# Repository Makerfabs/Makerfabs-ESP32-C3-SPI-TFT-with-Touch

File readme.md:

# Makerfabs ESP32-C3 SPI TFT with Touch

```c++
/*
Version:		V1.3
Author:			Vincent
Create Date:	2022/9/23
Note:
		2022/10/13	V1.1: Add example
		2022/10/18	V1.2: Add Line Chart demo
		2022/12/29	V1.3: Change wiki link
*/
```

[toc]

# Makerfabs

[Makerfabs home page](https://www.makerfabs.com/)

[Makerfabs Wiki](https://wiki.makerfabs.com/)

# Makerfabs ESP32-C3 SPI TFT with Touch
## Intruduce

Product Link ：[ESP32-C3 SPI TFT with Touch 3.5'' ILI9488](https://www.makerfabs.com/ep32-c3-risc-v-spi-tft-touch.html)

Wiki Link : [ESP32-C3_SPI_TFT_with_Touch](https://wiki.makerfabs.com/ESP32_C3_SPI_3.5_TFT_with_Touch.html)

Makerfabs ESP32-C3 TFT Touch equips with ESP32-C3, which is a single-core Wi-Fi and Bluetooth 5 (LE) microcontroller SoC, built around a 32-bit **RISC-V** chip processor with a four-stage pipeline that operates at up to 160 MHz, with 4MB Flash, 400KB SRAM. 

Being a number of the Makerfabs ESP Display family, this ESP32 C3 SPI 3.5 inch Touch is 320*480, with ILI9488 driver. Same as the other Makerfab's ESP32 displays, there 2 USB connectors, one for USB2UART convertor, and 1 USB native; on-board SD card, and Mabee connector(I2C) which is Seeedstudio Grove compatible, so it fits for applications that need sensor connected.

## Feature

- Controller: ESP32-C3-MINI-1-N4, 4MB Flash, RISCV-32bit, 160MHz, 400KB SRAM, Bluetooth 5
- Wireless: WiFi & Bluetooth 5.0
- LCD: 3.5inch TFT LCD
- Resolution: 480*320
- Color: RGB
- LCD interface: SPI
- LCD Driver: ili9488
- Touch Panel: Capacitive
- Touch Panel Driver: FT6236
- USB: Dual USB Type-C(one for USB-to-UART and one for native USB)
- USB2UART Chip: CP2104
- Power Supply: USB Type-C 5.0V(4.0V~5.25V)
- Button: Flash button and reset button
- Mabee interface: 1*I2C
- Backlight Controller: Yes
- MicroSD: Yes
- Arduino support: Yes
- Type-C Power Delivery: Not Supported
- Operation temperature: -40℃ to +85℃
- Dimension: 66mm * 84.3mm * 12mm
- Weight: 52g

# Code Explain

## Complier Option

- Install board : ESP32 .
- Install library : LovyanGFX library. 
- Use type-c use cable connect USB-TTL to PC.
- Upload codes, select "ESP32-C3 DEV Module"

## Firmware

### c3_9488

A simple test procedure. Touch the black area in the middle of the screen, and the screen starts showing solid colors in turn. Finally, an SD card image is displayed.

## Example

### Mabee CO2 Display

SGP30 and SHT31 sensor values are displayed on the screen. Use [Mabee CO2](https://www.makerfabs.com/mabee-tvoc-and-eco2-sgp30-sht31.html) sensor.

Need libraries:

- Adafruit_SGP30
- Adafruit_SHT31

### TVOC line chart

Shows a line chart of TVOC

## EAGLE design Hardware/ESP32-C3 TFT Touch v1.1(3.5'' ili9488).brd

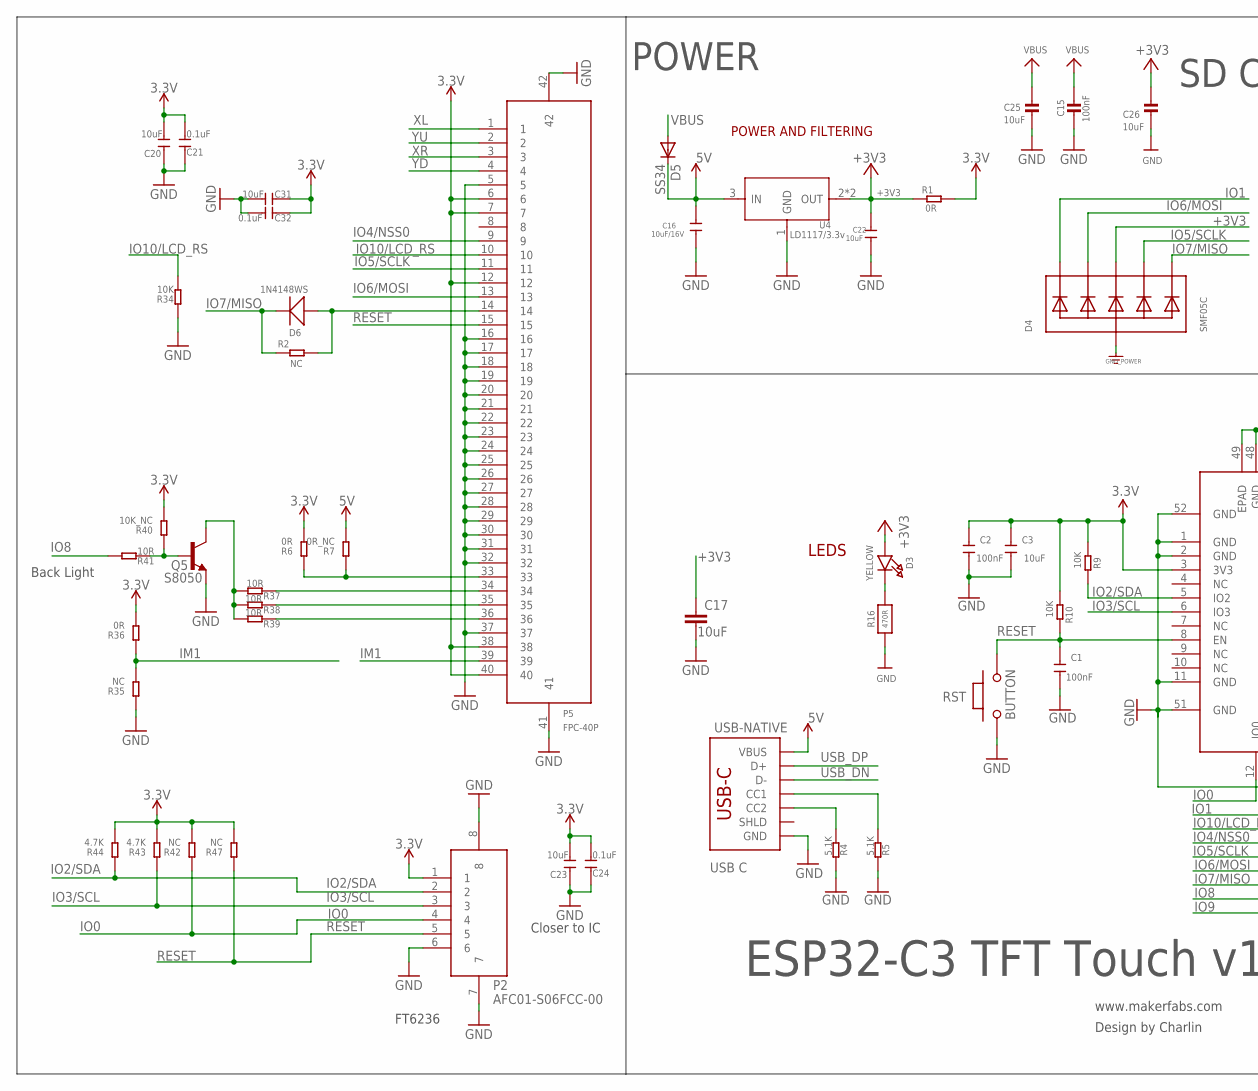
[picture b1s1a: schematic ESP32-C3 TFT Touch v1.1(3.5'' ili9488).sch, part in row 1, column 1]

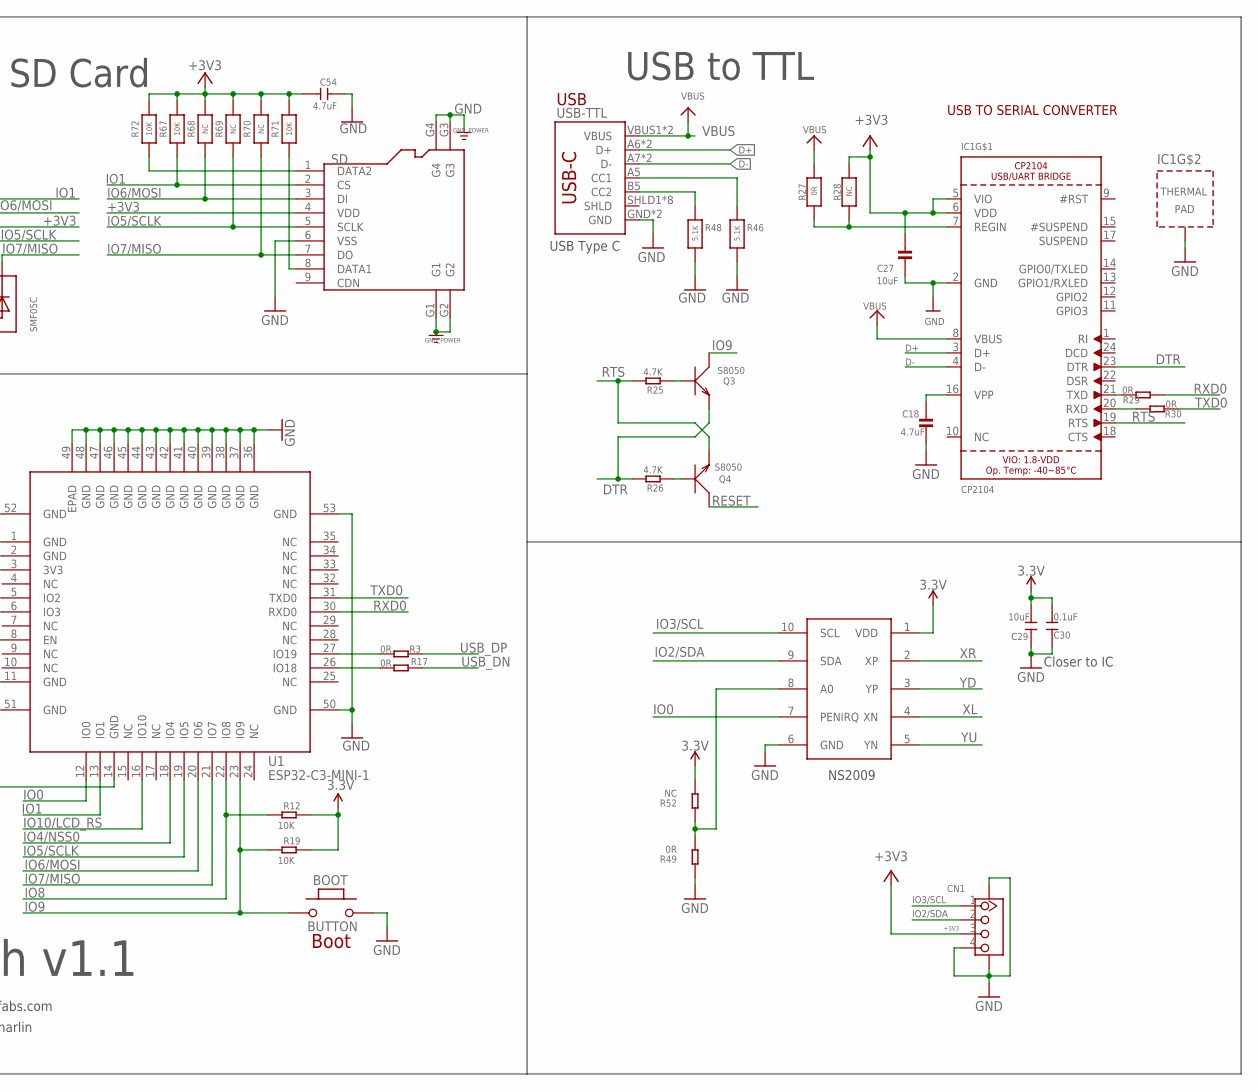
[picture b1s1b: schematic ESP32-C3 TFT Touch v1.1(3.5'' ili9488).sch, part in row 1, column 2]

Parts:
BOOT: BUTTON; 157SW
C1, C2: 100nF; C0603
C3, C17, C22: 10uF; C0603
C15: 100nF; 0603-NO
C16: 10uF/16V; C0603
C18: 4.7uF; 0603-NO
C20, C23, C29, C31: 10uF; DISCRETE_C0603
C21, C24, C30, C32: 0.1uF; DISCRETE_C0603
C25, C26, C27: 10uF; 0603-NO
C54: 4.7uF; DISCRETE_C0603
CN1: GROVE-CONNECTOR-SMD'90D'; HW4-SMD-2.0-90D
D3: YELLOW; CHIPLED_0805_NOOUTLINE
D4: SMF05C; SOT363
D5: SS34; DO-214AC
D6: 1N4148WS; SOD323
IC1: CP2104; QFN24_4MM_SMSC
P2: AFC01-S06FCC-00; SMD8-50P-740L535W
P5: FPC-40P; SMD42-50P-2560L490W
Q3, Q4: S8050; SOT23
Q5: S8050; SPARKFUN_SOT23
R1, R3, R17, R29, R30: 0R; R0603
R2: NC; R0603
R4, R5: 5.1K; R0603
R6, R36, R49: 0R; DISCRETE_R0603
R7: 0R_NC; DISCRETE_R0603
R9, R10, R12, R19: 10K; R0603
R16: 470R; 0603-NO
R25, R26: 4.7K; R0603
R27: 0R; 0603-NO
R28, R68, R69, R70: NC; 0603-NO
R34: 10K; DISCRETE_R0603
R35, R42, R47, R52: NC; DISCRETE_R0603
R37, R38, R39, R41: 10R; DISCRETE_R0603
R40: 10K_NC; DISCRETE_R0603
R43, R44: 4.7K; DISCRETE_R0603
R46, R48: 5.1K; 0603-NO
R67, R71, R72: 10K; 0603-NO
RST: BUTTON; 157SW
SD: HOLDER-MICROSD-9P; 9P-SMD-W/-RING
U1: ESP32-C3-MINI-1
U4: LD1117/3.3v; SOT89
U8: NS2009; MSOP10
USB-NATIVE: USB C; USB-C-16P-4LAYER-ISOLATED
USB-TTL: USB_C5; USB-C-16P-5

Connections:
3.3V: C2.2, C3.2, C20.2, C21.2, C23.2, C24.2, C29.2, C30.2, C31.1, C32.1, P2.1, P5.6, P5.7, P5.12, P5.38, P5.40, R1.2, R6.2, R9.1, R10.1, R12.2, R19.2, R36.2, R40.2, R42.2, R43.2, R44.2, R47.2, R52.2, U1.3 (3V3), U8.1 (VDD)
5V: C16.1, D5.C, R7.2, U4.3 (IN), USB-NATIVE.VBUS1 (VBUS), USB-NATIVE.VBUS2 (VBUS)
+3V3: C17.1, C22.1, C26.1, C27.1, C54.2, CN1.3, D3.A, D4.4 (C3), IC1.5 (VIO), IC1.6 (VDD), R1.1, R28.1, R67.2, R68.2, R69.2, R70.2, R71.2, R72.2, SD.4 (VDD), U4.2 (OUT), U4.4 (OUT)
D+: IC1.3 (D+), USB-TTL.A6 (D+), USB-TTL.B6 (D+)
D-: IC1.4 (D-), USB-TTL.A7 (D-), USB-TTL.B7 (D-)
DTR: IC1.23 (DTR), Q3.2 (E), R26.2
GND: BOOT.2, C1.1, C2.1, C3.1, C15.2, C16.2, C17.2, C18.2, C20.1, C21.1, C22.2, C23.1, C24.1, C25.2, C26.2, C27.2, C29.1, C30.1, C31.2, C32.2, C54.1, CN1.4, CN1.SS1, CN1.SS2, D4.2 (A), IC1.2 (GND), IC1.THERM (TP), P2.6, P2.7, P2.8, P5.5, P5.16, P5.17, P5.18, P5.19, P5.20, P5.21, P5.22, P5.23, P5.24, P5.25, P5.26, P5.27, P5.28, P5.29, P5.30, P5.31, P5.32, P5.37, P5.41, P5.42, Q5.2 (E), R4.1, R5.1, R16.1, R34.1, R35.1, R46.2, R48.2, R49.1, RST.1, SD.6 (VSS), SD.G1, SD.G2, SD.G3, SD.G4, U1.1 (GND), U1.2 (GND), U1.11 (GND), U1.14 (GND), U1.36 (GND), U1.37 (GND), U1.38 (GND), U1.39 (GND), U1.40 (GND), U1.41 (GND), U1.42 (GND), U1.43 (GND), U1.44 (GND), U1.45 (GND), U1.46 (GND), U1.47 (GND), U1.48 (GND), U1.49 (EPAD), U1.50 (GND), U1.51 (GND), U1.52 (GND), U1.53 (GND), U4.1 (GND), U8.6 (GND), USB-NATIVE.GND, USB-NATIVE.GND2 (GND), USB-TTL.GND, USB-TTL.GND2 (GND)
IM1: P5.39, R35.2, R36.1
IO0: P2.4, R42.1, U1.12 (IO0), U8.7 (PENIRQ)
IO1: D4.1 (C1), R67.1, SD.2 (CS), U1.13 (IO1)
IO2/SDA: CN1.2, P2.2, R9.2, R44.1, U1.5 (IO2), U8.9 (SDA)
IO3/SCL: CN1.1, P2.3, R43.1, U1.6 (IO3), U8.10 (SCL)
IO4/NSS0: P5.9, U1.18 (IO4)
IO5/SCLK: D4.5 (C4), P5.11, R69.1, SD.5 (SCLK), U1.19 (IO5)
IO6/MOSI: D4.3 (C2), P5.13, R68.1, SD.3 (DI), U1.20 (IO6)
IO7/MISO: D4.6 (C5), D6.-, R2.1, R70.1, SD.7 (DO), U1.21 (IO7)
IO8: R12.1, R41.2, U1.22 (IO8)
IO9: BOOT.1, Q3.3 (C), R19.1, U1.23 (IO9)
IO10/LCD_RS: P5.10, R34.2, U1.16 (IO10)
unnamed: C18.1, IC1.16 (VPP)
unnamed: Q4.1 (B), R26.1
unnamed: Q3.1 (B), R25.1
unnamed: D6.+, P5.14, R2.2
unnamed: D3.C, R16.2
unnamed: R46.1, USB-TTL.A5 (CC1)
unnamed: R48.1, USB-TTL.B5 (CC2)
unnamed: IC1.7 (REGIN), R27.2, R28.2
unnamed: R3.1, U1.27 (IO19)
unnamed: R5.2, USB-NATIVE.A5 (CC1)
unnamed: R4.2, USB-NATIVE.B5 (CC2)
unnamed: R17.1, U1.26 (IO18)
unnamed: IC1.21 (TXD), R29.2
unnamed: IC1.20 (RXD), R30.2
unnamed: P5.34, R37.1
unnamed: P5.35, R38.1
unnamed: P5.36, R39.1
unnamed: Q5.1 (B), R40.1, R41.1
unnamed: Q5.3 (C), R37.2, R38.2, R39.2
unnamed: R49.2, R52.1, U8.8 (A0)
unnamed: P5.33, R6.1, R7.1
unnamed: R72.1, SD.1 (DATA2)
unnamed: R71.1, SD.8 (DATA1)
RESET: C1.2, P2.5, P5.15, Q4.3 (C), R10.2, R47.1, RST.2, U1.8 (EN)
RTS: IC1.19 (RTS), Q4.2 (E), R25.2
RXD0: R29.1, U1.30 (RXD0)
TXD0: R30.1, U1.31 (TXD0)
USB_DN: R17.2, USB-NATIVE.A7 (D-), USB-NATIVE.B7 (D-)
USB_DP: R3.2, USB-NATIVE.A6 (D+), USB-NATIVE.B6 (D+)
VBUS: C15.1, C25.1, D5.A, IC1.8 (VBUS), R27.1, USB-TTL.VBUS1 (VBUS), USB-TTL.VBUS2 (VBUS)
XL: P5.1, U8.4 (XN)
XR: P5.3, U8.2 (XP)
YD: P5.4, U8.3 (YP)
YU: P5.2, U8.5 (YN)

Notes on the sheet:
www.makerfabs.com
Design by Charlin
USB
LEDS
POWER AND FILTERING
USB TO SERIAL CONVERTER
ESP32-C3 TFT Touch v1.1
POWER
USB to TTL
USB Type C
SD Card
NS2009
FT6236
Closer to IC
Back Light
Boot

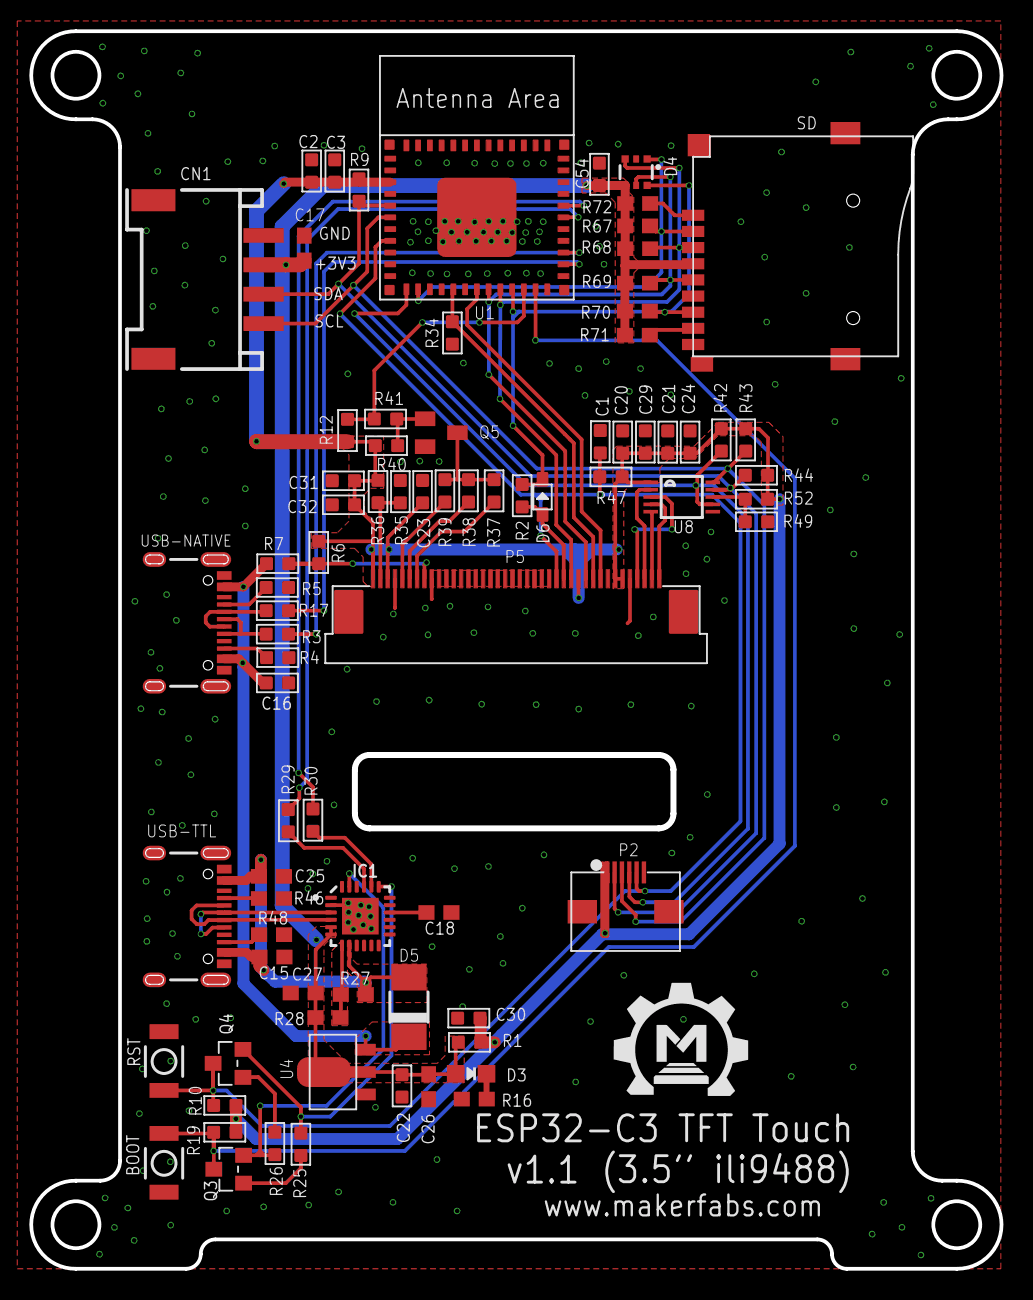
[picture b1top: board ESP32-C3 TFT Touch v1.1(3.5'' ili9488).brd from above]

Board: 2 copper layers, 66.1 x 84.3 mm, 81 parts (0 on the bottom side), 53 nets.

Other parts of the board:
U$1: MAKERFABS_0.3

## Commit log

2022-09-12 Create Project
2022-09-15 hardware
    Schematic and PCB v1.1
2022-09-23 Add readme
2022-10-13 Add example
2022-10-18 V1.2 line chart demo

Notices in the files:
parts and their libraries:
microbuilder: This work is placed in the public domain, and may be freely used for commercial and non-commercial work with the following conditions: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
SparkFun-Connectors: Licensing: Creative Commons ShareAlike 4.0 International - https://creativecommons.org/licenses/by-sa/4.0
